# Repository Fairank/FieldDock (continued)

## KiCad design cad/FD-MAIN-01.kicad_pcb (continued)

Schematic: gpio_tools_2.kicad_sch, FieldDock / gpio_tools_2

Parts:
R710, R711, R712: 51R; R_0402_1005Metric
R713: 0R; R_0402_1005Metric
R714: 226k 1% / ~120mA limit; R_0402_1005Metric
R715: 10k; R_0402_1005Metric
R716: 10k output bleed; R_0402_1005Metric
R717, R718: DNP 4.7k I2C pullup; R_0402_1005Metric
TP700: TARGET_POWER_FAULT_N; TestPoint_Pad_D1.0mm

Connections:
EXT_TARGET_IO2: R710.1; also elsewhere on the board
EXT_TARGET_IO3: R711.1; also elsewhere on the board
EXT_TARGET_IO4: R712.1; also elsewhere on the board
GND: R713.2, R714.2, R716.2; also elsewhere on the board
HDR_GND_GUARD: R713.1; also elsewhere on the board
HDR_TARGET_IO2: R710.2; also elsewhere on the board
HDR_TARGET_IO3: R711.2; also elsewhere on the board
HDR_TARGET_IO4: R712.2; also elsewhere on the board
HDR_TARGET_SCL: R717.2; also elsewhere on the board
HDR_TARGET_SDA: R718.2; also elsewhere on the board
TARGET_ILIM: R714.1; also elsewhere on the board
TARGET_POWER_FAULT_N: R715.2, TP700.1; also elsewhere on the board
V3V3: R715.1; also elsewhere on the board
V3V3_TARGET: R716.1, R717.1, R718.1; also elsewhere on the board

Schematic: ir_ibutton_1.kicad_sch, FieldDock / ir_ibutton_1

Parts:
C710, C713: 1u 10V X7R; C_0603_1608Metric
C711: 4.7u 10V X7R; C_0603_1608Metric
C712: 100n 10V X7R; C_0402_1005Metric_FieldDock_NoSilk
C714: 100n 10V X7R; C_0402_1005Metric
D710, D711, D712: VSMY14940 940nm; Vishay_VSMY14940
D713: BAT54WS-7-F; D_SOD-323
D714: TPD2EUSB30DRTR; Texas_DRT-3
J710: iButton contact probe / DATA GND; Antenna_2Pad_2mm
Q710: DMN2058UW-7; SOT-323_SC-70
Q711: DMN2004K-7; SOT-23
R719, R724, R726, R729, R7100: 100R; R_0402_1005Metric
R720, R725, R727, R730: 100k; R_0402_1005Metric
R721, R722, R723: 82R 1% 0.25W; R_0805_2012Metric
R728: 4.7k; R_0402_1005Metric
U710: TPS22919DCKR; SOT-363_SC-70-6
U711, U713: SN74LVC1G08DBVR; SOT-23-5
U712: TSOP75338TR; Vishay_TSOP753_TR

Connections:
CORE5: C710.1, U710.1 (IN); also elsewhere on the board
EXT_IBTN_EDGE: R729.2; also elsewhere on the board
EXT_IR_EDGE: U712.3 (OUT_N); also elsewhere on the board
GND: C710.2, C711.2, C712.2, C713.2, C714.2, D714.2 (D-), D714.3 (GND), J710.2, Q710.2 (S), Q711.2 (S), R720.2, R727.2, U710.2 (GND), U711.3 (GND), U712.1 (GND_1), U712.4 (GND_4), U713.3 (GND); also elsewhere on the board
IBTN_BUS: D714.1 (D+), J710.1, Q711.3 (D), R728.2, R729.1
IBTN_DRIVE: U713.1; also elsewhere on the board
IBTN_DRIVE_GATED: R726.1, U713.4
IBTN_EDGE: R730.1; also elsewhere on the board
IBTN_GATE: Q711.1 (G), R726.2, R727.1
IBTN_PULLUP_SOURCE: D713.1 (K), R728.1
IR_CARRIER: U711.1; also elsewhere on the board
IR_DRIVE_GATED: R719.1, U711.4
IR_EDGE: R725.1; also elsewhere on the board
IR_GATE: Q710.1 (G), R719.2, R720.1
IR_LED_A0: D710.2 (A), R721.2
IR_LED_A1: D711.2 (A), R722.2
IR_LED_A2: D712.2 (A), R723.2
IR_LED_K: D710.1 (K), D711.1 (K), D712.1 (K), Q710.3 (D)
IR_VS: C713.1, R724.2, U712.2 (VS)
TOOLS5: C711.1, D713.2 (A), R721.1, R722.1, R723.1, R7100.1, U710.6 (OUT)
TOOLS5_QOD: R7100.2, U710.5 (QOD)
TOOLS_IO_ENABLED: U710.3 (ON), U711.2, U713.2; also elsewhere on the board
V3V3: C712.1, C714.1, R725.2, R730.2, U711.5 (VCC), U713.5 (VCC); also elsewhere on the board
V3V3_RF: R724.1; also elsewhere on the board

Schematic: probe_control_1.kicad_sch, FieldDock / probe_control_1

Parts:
C730, C731, C732: 100n 10V X7R; C_0402_1005Metric
D730, D731, D732: TPD2EUSB30DRTR; Texas_DRT-3
J730: SM08B-GHS-TB(LF)(SN) AUX powered probe; JST_GH_SM08B-GHS-TB_1x08-1MP_P1.25mm_Horizontal
R731: 100k; R_0402_1005Metric
R732: 10k; R_0402_1005Metric
R733, R734, R735, R736, R737: 51R; R_0402_1005Metric
U730: SN74LVC1G08DBVR; SOT-23-5
U731: SN74LVC1G04DBVR; SOT-23-5
U732: SN74CB3T3245PWR; TSSOP-20_4.4x6.5mm_P0.65mm

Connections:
CSI_IRQ: U732.4 (A3); also elsewhere on the board
CSI_REQUEST: R731.1, U730.2, U732.5 (A4); also elsewhere on the board
CSI_RX: U732.3 (A2); also elsewhere on the board
CSI_TX: U732.2 (A1); also elsewhere on the board
EXT_AUX_CAPTURE: R737.1; also elsewhere on the board
EXT_LOAD_ENABLE: U730.1; also elsewhere on the board
EXT_PROBE5: J730.1; also elsewhere on the board
GND: C730.2, C731.2, C732.2, D730.3 (GND), D731.3 (GND), D732.2 (D-), D732.3 (GND), J730.2, J730.8, R731.2, U730.3 (GND), U731.3 (GND), U732.10 (GND); also elsewhere on the board
PLUG_CAPTURE: D732.1 (D+), J730.6, R737.2
PLUG_CSI_IRQ: D731.1 (D+), J730.5, R735.2
PLUG_CSI_REQUEST: D731.2 (D-), J730.7, R736.2
PLUG_CSI_RX: D730.2 (D-), J730.4, R734.2
PLUG_CSI_TX: D730.1 (D+), J730.3, R733.2
PROBE_BUS_DISABLE: R732.2, U731.4, U732.19 (OE_N)
PROBE_CSI_IRQ: R735.1, U732.16 (B3)
PROBE_CSI_REQUEST: R736.1, U732.15 (B4)
PROBE_CSI_RX: R734.1, U732.17 (B2)
PROBE_CSI_TX: R733.1, U732.18 (B1)
PROBE_IO_ENABLED: U730.4, U731.2
V3V3: C730.1, C731.1, C732.1, R732.1, U730.5 (VCC), U731.5 (VCC), U732.20 (VCC); also elsewhere on the board

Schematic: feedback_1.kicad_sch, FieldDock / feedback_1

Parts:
BZ740: PKMCS0909E4000-R1; Murata_PKMCS0909
C740, C742: 100n 10V X7R; C_0402_1005Metric
C741: 100n 16V X7R series AC; C_0603_1608Metric
D740: 1N4148W-7-F flyback; D_SOD-123
J740: 3V 8x2mm coin motor / wire attach; Antenna_2Pad_2mm
Q740: DMN2058UW-7; SOT-323_SC-70
R740, R742: 100R; R_0402_1005Metric
R741, R743: 100k; R_0402_1005Metric
U740, U741: SN74LVC1G08DBVR; SOT-23-5

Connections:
BEEP_AC: C741.2, R740.1
BEEP_OUT: C741.1, U740.4
BEEP_P: BZ740.1 (+), R740.2, R741.1
BEEP_PWM: U740.1; also elsewhere on the board
GND: BZ740.2 (-), C740.2, C742.2, Q740.2 (S), R741.2, R743.2, U740.3 (GND), U741.3 (GND); also elsewhere on the board
TOOLS_ENABLE: U740.2, U741.2; also elsewhere on the board
V3V3: C740.1, C742.1, U740.5 (VCC), U741.5 (VCC); also elsewhere on the board
V3V3_RF: D740.1 (K), J740.1; also elsewhere on the board
VIBRO_EN: U741.1; also elsewhere on the board
VIBRO_GATE: Q740.1 (G), R742.2, R743.1
VIBRO_GATED: R742.1, U741.4
VIBRO_LOW: D740.2 (A), J740.2, Q740.3 (D)

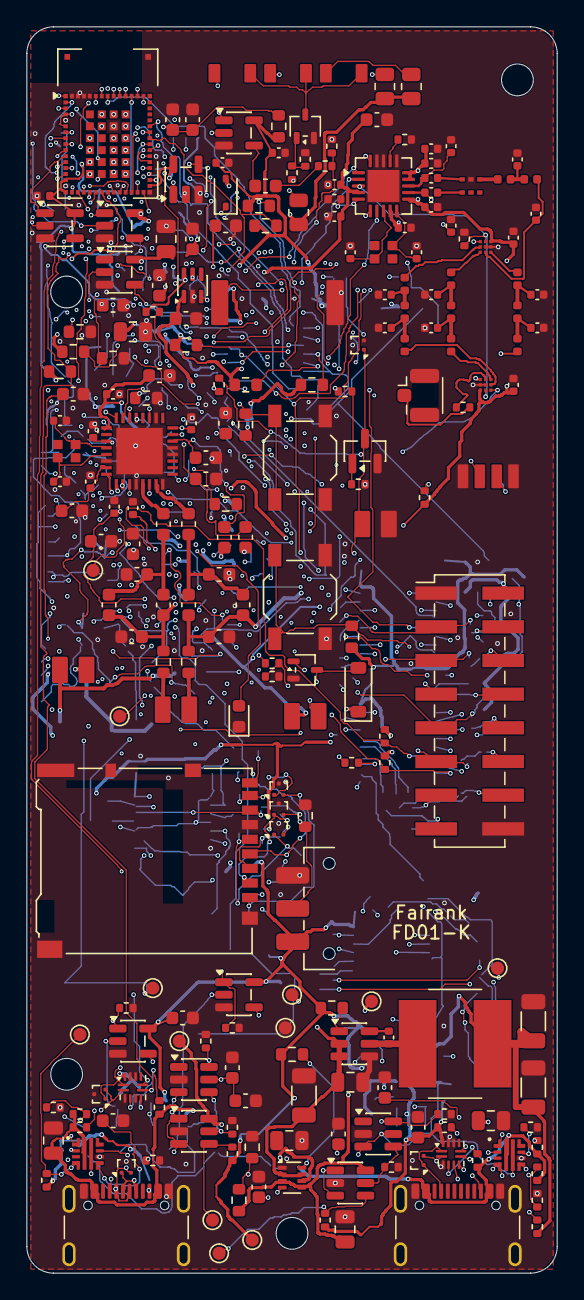
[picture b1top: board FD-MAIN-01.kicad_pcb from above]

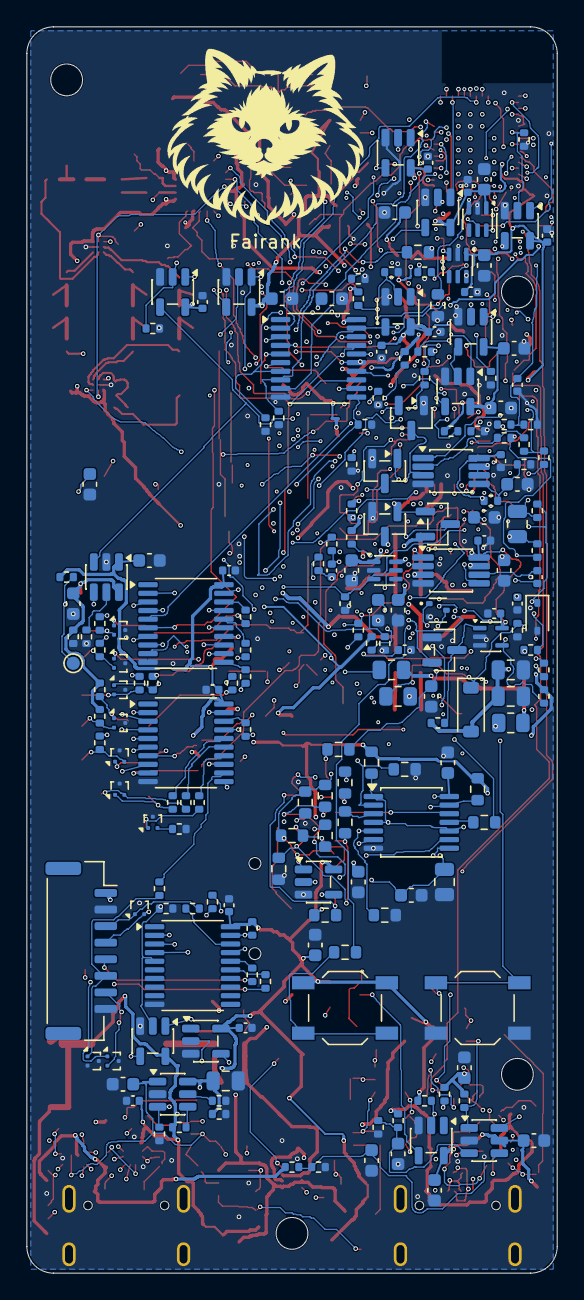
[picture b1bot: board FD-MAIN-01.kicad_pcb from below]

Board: 8 copper layers, 40.0 x 94.0 mm, 424 parts (196 on the bottom side), 271 nets.

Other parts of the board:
H1, H2, H3, H4: M2; MountingHole_2.4mm_M2

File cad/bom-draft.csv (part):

Reference,Value,Footprint,Section,Status
U1,STM32WB5MMGH6TR,RF_Module:ST-SiP-LGA-86-11x7.3mm,mcu,Engineering revision C
U2,SN74LVC1G08DBVR,Package_TO_SOT_SMD:SOT-23-5,controls,Engineering revision C
R1,0R analog feed,Resistor_SMD:R_0603_1608Metric,mcu,Engineering revision C
R2,10k BOOT pulldown,Resistor_SMD:R_0603_1608Metric,mcu,Engineering revision C
R3,10k,Resistor_SMD:R_0603_1608Metric,controls,Engineering revision C
R4,10k,Resistor_SMD:R_0603_1608Metric,controls,Engineering revision C
R5,100k,Resistor_SMD:R_0603_1608Metric,controls,Engineering revision C
R6,100k,Resistor_SMD:R_0603_1608Metric,controls,Engineering revision C
R7,100k,Resistor_SMD:R_0603_1608Metric,controls,Engineering revision C
R8,4.7k,Resistor_SMD:R_0603_1608Metric,mcu,Engineering revision C
R9,4.7k,Resistor_SMD:R_0603_1608Metric,mcu,Engineering revision C
R10,47k,Resistor_SMD:R_0603_1608Metric,mcu,Engineering revision C
R11,47k,Resistor_SMD:R_0603_1608Metric,mcu,Engineering revision C
R12,47k,Resistor_SMD:R_0603_1608Metric,mcu,Engineering revision C
R13,47k,Resistor_SMD:R_0603_1608Metric,mcu,Engineering revision C
R14,10k,Resistor_SMD:R_0603_1608Metric,mcu,Engineering revision C
R15,1k BOOT series,Resistor_SMD:R_0603_1608Metric,controls,Engineering revision C
R16,1k LED,Resistor_SMD:R_0603_1608Metric,controls,Engineering revision C
C1,4.7u 10V X7R,Capacitor_SMD:C_0805_2012Metric,mcu,Engineering revision C
C2,100n 10V X7R,Capacitor_SMD:C_0603_1608Metric,mcu,Engineering revision C
C3,1u 10V X7R,Capacitor_SMD:C_0603_1608Metric,mcu,Engineering revision C
C4,10n 10V X7R,Capacitor_SMD:C_0603_1608Metric,mcu,Engineering revision C
C5,100n RESET,Capacitor_SMD:C_0603_1608Metric,mcu,Engineering revision C
C6,100n USB supply,Capacitor_SMD:C_0603_1608Metric,mcu,Engineering revision C
C7,100n gate supply,Capacitor_SMD:C_0603_1608Metric,controls,Engineering revision C
C8,10u 10V X7R,Capacitor_SMD:C_0805_2012Metric,mcu,Engineering revision C
SW1,RESET,Button_Switch_SMD:SW_SPST_TL3342,controls,Engineering revision C
SW2,CONFIRM,Button_Switch_SMD:SW_SPST_TL3342,controls,Engineering revision C
SW3,STOP_REQUEST,Button_Switch_SMD:SW_SPST_TL3342,controls,Engineering revision C
SW4,HARD_DISABLE / ALLOW,Button_Switch_SMD:SW_SPDT_CK_JS102011SAQN,controls,Engineering revision C
SW5,BOOT_HOLD,Button_Switch_SMD:SW_SPST_TL3342,controls,Engineering revision C
D1,STATUS_LED,LED_SMD:LED_0603_1608Metric,controls,Engineering revision C
U201,TPS2116DRLR,Package_TO_SOT_SMD:SOT-583-8,core_power,Engineering revision C
R201,330k 1%,Resistor_SMD:R_0603_1608Metric,core_power,Engineering revision C
R202,100k 1%,Resistor_SMD:R_0603_1608Metric,core_power,Engineering revision C
R203,10k 1%,Resistor_SMD:R_0603_1608Metric,core_power,Engineering revision C
C201,4.7u 10V X7R,Capacitor_SMD:C_0805_2012Metric,core_power,Engineering revision C
C202,4.7u 10V X7R,Capacitor_SMD:C_0805_2012Metric,core_power,Engineering revision C
C203,22u 10V X7R,Capacitor_SMD:C_1206_3216Metric,core_power,Engineering revision C
U202,AP63203WU-7,Package_TO_SOT_SMD:TSOT-23-6,core_power,Engineering revision C
L201,4.7uH SRN8040TA-4R7M,Inductor_SMD:L_Bourns_SRN8040TA,core_power,Engineering revision C
C204,100n 25V X7R,Capacitor_SMD:C_0402_1005Metric,core_power,Engineering revision C
C205,10u 10V X7R,Capacitor_SMD:C_0805_2012Metric,core_power,Engineering revision C
C206,22u 10V X7R,Capacitor_SMD:C_1206_3216Metric,core_power,Engineering revision C
C207,22u 10V X7R,Capacitor_SMD:C_1206_3216Metric,core_power,Engineering revision C
R204,0R FB sense,Resistor_SMD:R_0603_1608Metric,core_power,Engineering revision C
J101,GCT USB4105-GF-A / PHONE USB2 FS + 5V,Connector_USB:USB_C_Receptacle_GCT_USB4105-xx-A_16P_TopMnt_Horizontal,phone_input,Engineering revision C
J102,GCT USB4105-GF-A / AUX 5V input only,Connector_USB:USB_C_Receptacle_GCT_USB4105-xx-A_16P_TopMnt_Horizontal,aux_input,Engineering revision C
D101,TPD2EUSB30DRTR,Package_TO_SOT_SMD:Texas_DRT-3,phone_input,Engineering revision C
U301,TPS22919DCKR,Package_TO_SOT_SMD:SOT-363_SC-70-6,storage,Engineering revision C
U302,"74LVC125APW,118 Nexperia",Package_SO:TSSOP-14_4.4x5mm_P0.65mm,storage,Engineering revision C
U303,SN74LVC1G32DBVR,Package_TO_SOT_SMD:SOT-23-5,storage,Engineering revision C
J301,DM3AT-SF-PEJM5,Connector_Card:microSD_HC_Hirose_DM3AT-SF-PEJM5,storage,Engineering revision C
D301,TPD2EUSB30DRTR,Package_TO_SOT_SMD:Texas_DRT-3,storage,Engineering revision C
D302,TPD2EUSB30DRTR,Package_TO_SOT_SMD:Texas_DRT-3,storage,Engineering revision C
D303,TPD2EUSB30DRTR,Package_TO_SOT_SMD:Texas_DRT-3,storage,Engineering revision C
R301,100R QOD,Resistor_SMD:R_0603_1608Metric,storage,Engineering revision C
R302,100k,Resistor_SMD:R_0603_1608Metric,storage,Engineering revision C
R303,22R clock damping,Resistor_SMD:R_0603_1608Metric,storage,Engineering revision C
R304,22R command damping,Resistor_SMD:R_0603_1608Metric,storage,Engineering revision C
R305,22R MISO damping,Resistor_SMD:R_0603_1608Metric,storage,Engineering revision C
R306,10k default isolated,Resistor_SMD:R_0603_1608Metric,storage,Engineering revision C
R307,47k,Resistor_SMD:R_0603_1608Metric,storage,Engineering revision C
R308,47k,Resistor_SMD:R_0603_1608Metric,storage,Engineering revision C
R309,47k,Resistor_SMD:R_0603_1608Metric,storage,Engineering revision C
R310,47k,Resistor_SMD:R_0603_1608Metric,storage,Engineering revision C
R311,47k,Resistor_SMD:R_0603_1608Metric,storage,Engineering revision C
R312,47k,Resistor_SMD:R_0603_1608Metric,storage,Engineering revision C
R313,1k detect series,Resistor_SMD:R_0603_1608Metric,storage,Engineering revision C
R314,100k,Resistor_SMD:R_0603_1608Metric,storage,Engineering revision C
R315,100k,Resistor_SMD:R_0603_1608Metric,storage,Engineering revision C
R316,10k,Resistor_SMD:R_0603_1608Metric,storage,Engineering revision C
C301,1u 10V X7R,Capacitor_SMD:C_0603_1608Metric,storage,Engineering revision C
C302,10u 10V X7R,Capacitor_SMD:C_0805_2012Metric,storage,Engineering revision C
C303,100n 10V X7R,Capacitor_SMD:C_0603_1608Metric,storage,Engineering revision C
C304,100n 10V X7R,Capacitor_SMD:C_0603_1608Metric,storage,Engineering revision C
C305,100n 10V X7R,Capacitor_SMD:C_0603_1608Metric,storage,Engineering revision C
C306,10n detect filter,Capacitor_SMD:C_0603_1608Metric,storage,Engineering revision C
U110,TUSB320LAIRWBR,Package_DFN_QFN:Texas_X2QFN-12_1.6x1.6mm_P0.4mm,phone_input,Engineering revision C
R110,887k 1%,Resistor_SMD:R_0402_1005Metric,phone_input,Engineering revision C
C110,100n 10V X7R,Capacitor_SMD:C_0603_1608Metric,phone_input,Engineering revision C
D110,TPD2EUSB30DRTR,Package_TO_SOT_SMD:Texas_DRT-3,phone_input,Engineering revision C
U111,TPS259470LRPWR,FieldDock:Texas_RPW0010A,phone_input,Engineering revision C
R112,470k 1%,Resistor_SMD:R_0402_1005Metric,phone_input,Engineering revision C
R113,34.8k 0.1%,Resistor_SMD:R_0402_1005Metric,phone_input,Engineering revision C
R114,10.0k 0.1%,Resistor_SMD:R_0402_1005Metric,phone_input,Engineering revision C
R115,6.65k 1%,Resistor_SMD:R_0402_1005Metric,phone_input,Engineering revision C
C111,1u 50V X7R,Capacitor_SMD:C_0805_2012Metric,phone_input,Engineering revision C
C112,10n 50V X7R,Capacitor_SMD:C_0603_1608Metric,phone_input,Engineering revision C
C113,1u 10V X7R,Capacitor_SMD:C_0603_1608Metric,phone_input,Engineering revision C
U112,TPS2553DBVR,Package_TO_SOT_SMD:SOT-23-6,phone_input,Engineering revision C
U113,TS5A3159ADBVR,Package_TO_SOT_SMD:SOT-23-6,phone_input,Engineering revision C
R116,64.9k 1%,Resistor_SMD:R_0402_1005Metric,phone_input,Engineering revision C
U114,SN74LVC1G08DBVR,Package_TO_SOT_SMD:SOT-23-5,phone_input,Engineering revision C
R117,100k 1%,Resistor_SMD:R_0402_1005Metric,phone_input,Engineering revision C
R118,100k 1%,Resistor_SMD:R_0402_1005Metric,phone_input,Engineering revision C
C114,100n 10V X7R,Capacitor_SMD:C_0603_1608Metric,phone_input,Engineering revision C
C115,100n 10V X7R,Capacitor_SMD:C_0603_1608Metric,phone_input,Engineering revision C
R119,100k 1%,Resistor_SMD:R_0402_1005Metric,phone_input,Engineering revision C
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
